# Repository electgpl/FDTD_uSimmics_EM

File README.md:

# qucs-em-viz

**EM simulation and visualization toolkit for RF structures on PCB: uSimmics / QucsStudio projects, KiCad boards and openEMS.**

Three independent scripts share one Python package (`qemviz/`). Each one solves a different problem in the design flow of an antenna or RF circuit on a PCB, from a 2D estimate in seconds to a full-wave 3D simulation of the board as manufactured.

*Left: 1×4 patch array of the HLK-LD2411 24 GHz radar (uSimmics flow). Right: 902–928 MHz directional coupler on FR4 (KiCad flow).*

---

## The three tools: which one do I use?

| Script | Input | Answers the question | Solver | Typical time |
|---|---|---|---|---|
| [`qucs_em_viz.py`](#1-qucs_em_vizpy--usimmics--qucsstudio-projects) | uSimmics `.pcb` + `.dat` | *How does the antenna I designed in uSimmics radiate, and what do its fields look like?* | uSimmics results; optional openEMS | seconds (minutes with openEMS) |
| [`kicad_em.py`](#2-kicad_empy--kicad-boards-n-port-full-wave) | KiCad `.kicad_pcb` + TOML sidecar | *How does the real board behave, with its connectors, pads, ground ring and vias?* | openEMS FDTD 3D | minutes |
| [`qs2d_mtl.py`](#3-qs2d_mtlpy--2d-quasi-static-solver--mtl) | Parameters in its CONFIG block | *What Z0, Z0e/Z0o, εeff and coupling do these line dimensions give?* | 2D Laplace + MTL | seconds |

**Suggested flow for an RF circuit (e.g. a directional coupler or a filter):**

```
 qs2d_mtl.py              uSimmics (+ qucs_em_viz.py)        KiCad layout              kicad_em.py            VNA
 size the lines      ->   design / iterate in the EM    ->   route the real    ->   verify the board   ->   measure and
 in seconds               solver, visualize results          board                  as manufactured         overlay .sNp
```

- **Antennas designed in uSimmics:** `qucs_em_viz.py`.
- **Couplers, filters, transitions or any N-port routed in KiCad:** `kicad_em.py`.
- **Quick dimensioning of single or coupled lines, or a reference curve for the 3D result:** `qs2d_mtl.py`.

All three scripts follow the same rules: parameters live in a `CONFIG` block at the top of the file, there are no command-line arguments (they run as-is from Thonny or any IDE), and relative paths are resolved from the script's own folder.

---

## Repository layout

```
qucs-em-viz/
├── qucs_em_viz.py          tool 1: uSimmics / QucsStudio projects
├── kicad_em.py             tool 2: KiCad boards -> openEMS N-port
├── qs2d_mtl.py             tool 3: 2D quasi-static + MTL
├── qemviz/                 shared package
│   ├── sexpr.py              S-expression reader (KiCad)
│   ├── model.py              neutral model: stackup, copper per layer, vias, ports, enclosure
│   ├── fe_kicad.py           KiCad front-end
│   ├── sidecar.py            TOML sidecar loader (stdlib tomllib) with defaults
│   ├── oe_backend.py         neutral model -> openEMS: mesh, boundaries, ports, N-port, cache
│   ├── fields.py             field dumps, |E| maps, phase animations (MP4/GIF)
│   ├── plots.py              layout, S-parameters, coupler metrics
│   ├── qs2d.py               2D quasi-static solver + MTL S-matrix
│   └── touchstone.py         .sNp writer / reader
├── examples/
│   ├── Radar24G_Array1x4_Layout.pcb / .dat     uSimmics example (24 GHz patch array)
│   └── coupler/
│       ├── DirectionalCoupler.kicad_pcb          KiCad example (4-port coupler)
│       └── DirectionalCoupler.toml               its sidecar
├── docs/img/               README figures
└── requirements.txt
```

`qucs_em_viz.py` is still a self-contained script. `kicad_em.py` and `qs2d_mtl.py` use the `qemviz/` package, so keep them next to that folder.

---

## Installation

```bash
pip install -r requirements.txt
```

| Package | Needed by |
|---|---|
| `numpy`, `matplotlib`, `pillow` | all |
| `h5py` | openEMS field dumps (tools 1 and 2) |
| `shapely` | `kicad_em.py` (polygon union, thermal-relief removal) |
| `scipy` | `qs2d_mtl.py` (sparse solver) |
| `imageio-ffmpeg` (optional) | MP4 animations in `kicad_em.py`, if `ffmpeg` is not in `PATH` |

### openEMS (tools 1 and 2)

The openEMS and CSXCAD Python bindings are not on PyPI. Install them from the [official openEMS releases](https://github.com/thliebig/openEMS-Project/releases) or build them following the [openEMS documentation](https://docs.openems.de/). The code was validated with openEMS v0.37.

**Windows:** since Python 3.8, DLLs are no longer searched in `PATH`. Both scripts register the openEMS folder automatically if they find `CSXCAD.dll` in `OE_DLL_DIR`, `%OPENEMS_INSTALL_PATH%`, `C:\openEMS` or `Program Files\openEMS`. If you get `DLL load failed while importing CSXCAD`, set in the CONFIG block:

```python
OE_DLL_DIR = r"C:\path\to\openEMS"   # folder containing openEMS.exe and CSXCAD.dll
```

---

## 1. `qucs_em_viz.py` — uSimmics / QucsStudio projects

Reads a uSimmics (formerly QucsStudio) **EM layout** project — the `.pcb` geometry and the binary `.dat` results — and produces layout, S11 and Smith chart, polar cuts and a 3D radiation pattern on top of the real copper. Through openEMS it also produces what uSimmics does not export: the **real near field** over the board, the surface current and the wave leaving the PCB. Ports, substrate and boundaries are taken from what you defined in uSimmics; nothing else has to be declared.

It is not tied to one antenna type: patch arrays, MIFA/IFA, printed dipoles, Yagis, filters and lines all work.

### Quick start

1. Simulate the layout in uSimmics (enable **Radiation** in the layout properties if you want the far-field from uSimmics).
2. In the CONFIG block:

```python
QUCS_DIR = r"C:\uSimmics\my_antenna"   # folder with the .pcb and .dat
PROJECT  = "my_antenna"                # base name of the files
```

3. Run it. Interactive windows open (the 3D pattern rotates with the mouse) and everything is saved to `<QUCS_DIR>/qucs_viz/`.

The repository is preconfigured to run `examples/Radar24G_Array1x4_Layout`.

### Outputs

| File | Content | Needs |
|---|---|---|
| `01_layout.png` | Copper from the `.pcb`, ports (with impedance), lumped shorts, size, substrate | `.pcb` |
| `02_s11.png` + `02_s11_<source>.csv` | \|S11\| in dB, ISM bands, −10 dB bandwidth; numeric export (f, S11, Zin) | `.dat` and/or openEMS |
| `03_smith.png` | S11 on a Smith chart | idem |
| `04_cuts_polar.png` | φ = 0° and φ = 90° cuts, HPBW, directivity | a pattern source |
| `05_pattern_3d.png` | 3D pattern (dB colormap) on the real copper | a pattern source |
| `06_field_map_db.png`, `wave.gif` | \|E\|·r and Re{E·e^jωt} on a vertical plane | a pattern source |
| `07_nearfield_E_top.png`, `nearfield.gif` | Real \|E\| just above the copper, static and animated | openEMS |
| `08_surface_current_J.png` | Current density \|J\| on the copper | openEMS |
| `09_nearfield_E_side.png`, `nearfield_side.gif` | \|E\|·r and the real wave on a vertical plane | openEMS |
| `pattern_3d_rot.gif` | Rotating 3D pattern (off by default) | `MAKE_ROT_GIF = True` |

### Pattern sources

`PATTERN_SOURCE = "auto"` tries, in order:

| Source | What it is | When |
|---|---|---|
| `dat` | Far-field computed by uSimmics (Radiation enabled) | Preferred whenever available; valid for any antenna |
| `openems` | Own openEMS run built from the `.pcb` primitives, with NF2FF and field dumps | Near fields and currents, or no far-field in the `.dat` |
| `patch` | Analytical patch (cavity model) × array factor | Quick look at patch arrays only |
| `none` | Layout and S-parameters only | — |

With a far-field in the `.dat`, openEMS is skipped unless `OE_NEARFIELD_ALWAYS = True` (then the pattern still comes from uSimmics and openEMS adds figures 07–09). The field map synthesized from a far-field is masked for `r < max(λ/2π, antenna size)`; between that radius and 2D²/λ it is an approximation (Fresnel region).

### Configuration

| Parameter | Default | Meaning |
|---|---|---|
| `PATTERN_SOURCE` | `"auto"` | `auto`, `dat`, `openems`, `patch`, `none` |
| `F_PATTERN_HZ` | `None` | Pattern frequency; `None` = Radiation frequency of the `.pcb` if inside the sweep, otherwise the S11 minimum |
| `CUT_PHI_DEG` | `None` | Plane for the field maps; `None` = plane of the narrowest beam |
| `DB_RANGE` | `30` | Dynamic range of the dB plots |
| `FIELD_HALF_LAM`, `FIELD_RES_LAM` | `5`, `1/30` | Size and resolution of the far-field-based map, in λ₀ |
| `MAKE_GIFS`, `MAKE_ROT_GIF`, `N_FRAMES` | `True`, `False`, `24` | Animations |
| `SHOW`, `SHOW_WAVE_LIVE` | `True`, `True` | Interactive windows |
| `PATCH_REGEX`, `POL_AXIS`, `ELEM_PHASE_DEG`, `ELEM_AMPL` | | Analytical patch model |
| `OE_ENABLE` | `True` | Allow openEMS in `auto` mode |
| `OE_NEARFIELD_ALWAYS` | `False` | Run openEMS for figures 07–09 even if the `.dat` has a far-field |
| `OE_GROUND` | `"auto"` | Bottom ground: follows the substrate backside flag of the `.pcb`; or `"full"`, `"none"`, `"largest"`, list of rectangles (m) |
| `OE_EXTRA_TOP` | `[]` | Extra top copper (m), e.g. the rest of the board ground |
| `OE_RES_MM` | `None` | Fine cell; `None` = half of the narrow traces, ≥ 2 cells per port |
| `OE_END_DB`, `OE_MAX_TS` | `-30`, `400000` | End criterion and timestep limit |
| `OE_AIR_LAM`, `OE_AIR_UP_LAM` | `0.25`, `1.0` | Air around / above the board, in λ at the lowest frequency |
| `OE_NEAR_DZ_MM`, `OE_N_FDUMP` | `0.5`, `21` | Height of the \|E\| plane, number of dump frequencies |
| `OE_WRITE_XML`, `OE_OPEN_APPCSXCAD`, `OE_VTK_DUMPS` | `True`, `False`, `False` | Model XML for AppCSXCAD; open it; time-domain VTK for ParaView |
| `OE_FORCE_RERUN` | `False` | Ignore the cache |

openEMS results are cached in `qucs_viz/openems_<hash>/`; the hash covers the `.pcb`, the openEMS settings and the backend version.

### How the uSimmics files are read

**`.pcb` (text):** `Rectangle NAME x y dx|dy|w|h` → copper in `[x+dx, x+dx+w] × [y+dy, y+dy+h]` (m). `Lumped NAME x y num dir Z … wx wy` → `num > 0` is a port, `num = 0` a lumped element (0 Ω = via to ground); `wx`, `wy` are the element widths. `Substrate` (εr, h, tan δ, copper thickness, backside metal flag), `Frequency` and `Radiation` complete the setup. Only `Rectangle` and `Lumped` primitives are supported for now.

**`.dat` (binary QucsData):** `"QucsData"` + 4 bytes + `int32` header length, header entries `[int32 type][int32 N][name\0][dependencies\0]`, then the data blocks in the same order. Block sizes come from the type code (3 = complex dependent, 7 = real dependent, 5 = real independent); for unknown codes the parser tries the combinations that match the file size exactly. Far-field axes `theta/phi` or `azimuth/elevation` are both recognized.

### Validation: 24 GHz patch array (`examples/`)

uSimmics FDTD vs. this openEMS backend (0.085 mm fine cell, 2.0 Mcells, −30 dB end criterion):

| | uSimmics | openEMS backend |
|---|---|---|
| S11 minimum | −15.53 dB @ 24.714 GHz | −16.71 dB @ 24.425 GHz |
| Zin at minimum | 41.6 − j13.0 Ω | 42.5 − j11.3 Ω |
| −10 dB bandwidth | 367 MHz | 443 MHz |

The ≈1.2 % resonance shift is consistent with two FDTD runs on different meshes over 0.17 mm traces. NF2FF at 24.125 GHz: D = 10.4 dBi, HPBW 37.6° (array plane) and 78.0° (orthogonal plane). The far-field parser was also checked with a synthetic `.dat` of an ideal short dipole: D = 1.76 dBi, HPBW = 90°.

---

## 2. `kicad_em.py` — KiCad boards, N-port full-wave

Reads a **KiCad 9 `.kicad_pcb`** directly (no KiCad installation or CLI needed) and simulates the board as manufactured in openEMS: SMA pads, tapers, ground rings and stitching vias included. It produces the full S-matrix, a Touchstone file to overlay with a VNA, coupler metrics, \|E\| maps and phase animations.

### What is defined where

KiCad only provides the **geometry**. Everything KiCad does not store goes in a **TOML sidecar** next to the board. There is nothing special to draw in KiCad.

| What | Where |
|---|---|
| Copper, vias, pads, board outline | `.kicad_pcb` |
| Material (εr, tan δ, thickness) | KiCad *Board Setup → Physical Stackup* if filled in; otherwise `[stackup]` in the sidecar |
| Ports | Automatic from coaxial-connector footprints; manual in `[ports]` |
| Excitation | Automatic: each port is excited in turn |
| Test environment (box, air, lid) | `[enclosure]` |
| Frequency sweep and band of interest | `[sweep]` |
| Mesh, field maps, animations | CONFIG block of `kicad_em.py` |

### Quick start

The repository is preconfigured with the coupler example. Open `kicad_em.py` and run it:

```python
KICAD_PCB = "examples/coupler/DirectionalCoupler.kicad_pcb"
SIDECAR   = "examples/coupler/DirectionalCoupler.toml"
OUT_DIR   = "examples/coupler/em_out"
```

For a new board:

1. Create a folder, e.g. `examples/filter_915/`, and put your `.kicad_pcb` in it.
2. Copy `DirectionalCoupler.toml` there with a new name and adapt `[stackup]`, `[sweep]`, `[enclosure]` and the port `order` (remove `[roles]` if it is not a coupler).
3. Point `KICAD_PCB`, `SIDECAR` and `OUT_DIR` to the new files and run.
4. **Check `01_layout.png` first**: every port (numbered red dot) must sit at the end of its connector pad, on the board edge. Fix any port with `[[ports.override]]` before trusting the results.

The first run simulates (a few minutes per excitation for the coupler); later runs use the cache and finish in seconds.

### Sidecar reference

```toml
name = "DirectionalCoupler"

[stackup]                 # used when the .kicad_pcb has no Physical Stackup
er = 4.4
tand = 0.02
h = 1.6                   # mm

[sweep]
f_start = 0.3e9
f_stop = 3.0e9
n_points = 541
band = [902e6, 928e6]     # shaded in the plots; also where tan(delta) is exact (see notes)

[geometry]
# roi = [110, 95, 170, 122]   # clip box in KiCad mm (optional)
thermal_close_mm = 0.3        # removes thermal reliefs (per-net morphological closing)
simplify_mm = 0.02

[ports]
auto = true               # from SMA / U.FL / MMCX / SMB / ... footprints, pad "1"
kind = "lumped"           # "lumped" (validated) | "msl" (experimental, not validated yet)
z0 = 50.0
order = ["J1", "J2", "J3", "J4"]   # port numbering: Port 1 = J1, ...

# Manual port (or override of an auto-detected one: same name = only the given fields change)
# [[ports.override]]
# name  = "IN"
# x     = 102.0          # KiCad mm
# y     = 102.0
# prop  = "+x"           # direction INTO the structure: "+x" "-x" "+y" "-y" (KiCad: +y = down)
# width = 3.0            # conductor width at the port
# z0    = 50.0

[roles]                   # only for couplers: enables coupling / isolation / directivity plots
input = "J1"
through = "J2"
coupled = "J3"
isolated = "J4"

[enclosure]
kind = "pec_box"          # closed metal box | "open" = free space with PML_8
air = 4.8                 # mm of air above the top copper
lid_h = 1.6               # lid dielectric thickness (0 = no lid)
lid_er = 4.4
lid_tand = 0.02
lid_metal = true          # copper on the outer face of the lid
# box = [100, 82, 180, 122]       # PEC side walls (KiCad mm); default = board outline
# frame_er = 4.4                  # dielectric frames between walls and an inner window
# frame_window = [103, 85, 177, 119]
```

**Ports.** Auto-detection takes pad "1" of every footprint whose library name matches SMA, U.FL, MMCX, SMB, SMP, IPEX or Coaxial. The reference plane is the end of the pad closest to the board edge, and the port is a vertical lumped port from the trace to the copper layer below. For boards without connectors (a filter between two traces, a section of a larger board), declare the ports manually.

**Excitation.** Nothing to declare. For the full S-matrix every port is excited in turn with a Gaussian pulse covering `[sweep]`, while the other ports are terminated in their Z0. With `SYMMETRY = "mirror_x"` (or `"mirror_y"`) in the CONFIG block the script pairs the ports by position and only excites one port per pair. `DUMP_PORT` selects which excitation is used for the field maps.

### Outputs (in `OUT_DIR`)

| File | Content |
|---|---|
| `01_layout.png` | Copper (top and bottom), vias, ports with their numbers, in KiCad coordinates |
| `02_sparams.png` | All \|Sij\| vs. frequency |
| `03_coupler_metrics.png` | Coupling, isolation, directivity, return loss, insertion loss, band shaded, overlays (MTL, VNA) — if `[roles]` is defined |
| `<name>.sNp` | Touchstone (RI, Hz, 50 Ω) |
| `04_E_top_<f>.png` | \|E\| top view in dB, turbo colormap, copper contours |
| `05_E_phase_<f>.mp4` / `.gif` | \|E(t)\| = \|Re{E·e^jφ}\| over one RF period: MP4 1920×1080, 24 fps, H.264 crf 16, 72 frames, plus GIF preview |
| `06_E_profile_<f>.png` | \|E\| along the lines listed in `PROFILES` |
| `oe_<hash>_exc<n>_model.xml` | openEMS model of each run (open it in AppCSXCAD to inspect geometry, mesh and ports) |

The console prints the in-band reciprocity error and a table of C / I / D / RL / IL at the band edges, band centre, 915 MHz and 1830 MHz for every overlaid source.

### Configuration

| Parameter | Default | Meaning |
|---|---|---|
| `KICAD_PCB`, `SIDECAR`, `OUT_DIR` | example | Input board, sidecar, output folder |
| `OE_DLL_DIR` | `None` | openEMS folder on Windows, if not found automatically |
| `SYMMETRY` | `"mirror_x"` | `None`, `"mirror_x"`, `"mirror_y"` |
| `FORCE_RERUN` | `False` | Ignore the cache |
| `MESH["res_mm"]` | `0.5` | Fine cell at copper edges (thirds rule) |
| `MESH["lambda_div"]` | `20` | Max cell = λ/20 at `f_stop` in the densest dielectric |
| `MESH["max_board_mm"]` | `1.0` | Max x/y cell (≥ 3 cells across gaps of coupled lines) |
| `MESH["n_sub"]`, `MESH["n_lid"]` | `4`, `2` | Cells across substrate and lid |
| `MESH["end_db"]`, `MESH["max_ts"]` | `-40`, `1e6` | End criterion and timestep limit |
| `DUMP_Z_FRAC` | `0.25` | Dump plane depth below the top copper, as a fraction of h |
| `DUMP_FREQS`, `DUMP_PORT` | `[915e6, 1830e6]`, `1` | Frequencies and excitation of the field maps |
| `VTK_TIME_DUMP` | `False` | Time-domain VTK of the same plane (ParaView animation of the pulse) |
| `MAKE_MP4`, `MAKE_GIF`, `ANIM_FRAMES` | `True`, `True`, `72` | Animations |
| `DB_RANGE` | `50` | Dynamic range of the \|E\| maps |
| `PROFILES` | coupled line | \|E\| cuts: `(label, (x0, y0), (x1, y1))` in KiCad mm |
| `OVERLAY_S4P` | MTL result | Extra Touchstone files plotted with the openEMS result (MTL, VNA) |

### Modelling notes

- **Coordinates:** KiCad's y points down; the model flips it internally and all plots and sidecar coordinates use KiCad coordinates.
- **Copper:** zero-thickness PEC sheets; segments with round caps; arcs every 10°; per-net union with morphological closing (removes thermal reliefs); polygons with holes are split for CSXCAD. Silkscreen, fab, courtyard, mask and text are ignored.
- **Vias:** z-directed PEC wires snapped to the nearest mesh line (no extra mesh lines, never silently dropped).
- **Mesh:** thirds rule (1/3 inside, 2/3 outside) on axis-aligned copper edges, `n_sub` cells per substrate, λ/20 limit, smoothing ratio 1.4, merging of near-coincident lines while keeping copper and port edges.
- **Boundaries:** `pec_box` = PEC on all six faces (the lid's outer copper is the top wall); `open` = PML_8 with λ/4 of air at the lowest frequency.
- **Dielectric loss:** openEMS models tan δ as a constant conductivity κ = 2πf·ε0·εr·tan δ, exact at one frequency only (tan δ_eff = tan δ·f_loss/f). The script sets f_loss at the centre of `band`; without it, the loss at the band would be wrong by the ratio of frequencies.

### Validation: directional coupler (`examples/coupler/`)

80 × 40 mm FR4 (εr 4.4, tan δ 0.02, 1.6 mm), 3 mm lines with a 3 mm gap, 38 mm coupled section, PEC box on the board outline, 4.8 mm of air, FR4 lid with outer copper, lumped 50 Ω ports at the SMA pad ends. Values at 915 MHz.

| Quantity | 2D/MTL (`qs2d_mtl.py`) | openEMS (`kicad_em.py`) |
|---|---|---|
| Z0 / Z0e / Z0o [Ω] | 48.9 / 51.1 / 46.8 | — |
| εeff,e / εeff,o | 3.354 / 3.097 | — |
| Coupling [dB] | 27.43 | 27.86 |
| Isolation [dB] | 31.74 | 31.29 |
| Directivity [dB] | 4.31 | 3.43 |
| Return loss [dB] | 32.9 | 20.5 |
| Insertion loss [dB] | 0.11 | 0.28 |
| Coupling peak | 27.10 dB @ 1.105 GHz | 27.55 dB @ 1.140 GHz |
| Directivity @ 1830 MHz [dB] | −7.0 | −8.9 |

Coupling and isolation agree within 0.5 dB. Return loss and insertion loss differ by construction: the MTL models only the straight coupled section, while openEMS includes the SMA pad launches (1.27 mm pad, taper and coplanar ground pads), the lumped-port inductance and the feed lines. In-band reciprocity error of the openEMS S-matrix: 1.2·10⁻³.

---

## 3. `qs2d_mtl.py` — 2D quasi-static solver + MTL

Two steps, no 3D simulation:

1. **2D quasi-static solver:** finite differences of ∇·(ε∇φ) = 0 on the cross-section of the lines, with layered dielectrics, an optional metal cover and side walls. Outputs per-unit-length C, L, G matrices and **Z0, Z0e/Z0o, εeff,e/εeff,o**: what a line calculator gives, but with enclosure, lid and multiple dielectrics.
2. **MTL model:** exact chain matrix of the coupled section (inhomogeneous lines, so different even and odd phase velocities) → 4-port S-matrix, exported as `.s4p`.

Use it to dimension lines in seconds (change width, gap, length or lid height and see coupling, directivity and the λ/4 frequency move), and as a reference curve for `kicad_em.py`, which overlays the `.s4p` automatically. Its geometry does not come from a PCB file: the cross-section is defined in the CONFIG block.

### Configuration

| Parameter | Example (coupler) | Meaning |
|---|---|---|
| `WIDTH_MM`, `SIDE_WALLS` | `40.0`, `True` | Cross-section width and PEC side walls |
| `H_MM`, `ER`, `TAND` | `1.6`, `4.4`, `0.02` | Substrate |
| `AIR_MM` | `4.8` | Air between top copper and lid |
| `LID_MM`, `LID_ER`, `LID_TAND`, `LID_METAL` | `1.6`, `4.4`, `0.02`, `True` | Lid (0 = none) and its outer copper (False = open top) |
| `STRIPS_MM` | `[(18.5, 21.5), (24.5, 27.5)]` | (y0, y1) of line 1 (main) and line 2 (coupled), from the left wall |
| `COUPLED_LEN_MM` | `38.0` | Length of the coupled section |
| `GRID_MM` | `0.05` | FD cell (≈1 % on Z0, a few seconds) |
| `F_START`, `F_STOP`, `N_POINTS`, `BAND` | | Sweep of the MTL S-matrix |
| `VARIANTS` | `True` | Also print lid → air and no-lid variants |
| `OUT_S4P` | `examples/coupler/em_out/mtl_qs2d.s4p` | Output Touchstone (ports: input, through, coupled, isolated) |

### Validation

Isolated 3 mm microstrip on 1.6 mm FR4 (εr 4.4): 50.5 Ω vs. 50.65 Ω from Hammerstad–Jensen (0.2 %), converging with the grid (48.71 → 48.88 → 48.97 Ω for 0.1 / 0.05 / 0.025 mm on the shielded coupler). For the coupler: removing the lid gives 24.4 dB of coupling instead of 27.4 dB, and replacing the FR4 lid by air changes it by 0.2 dB.

---

## Overlaying VNA measurements

`qemviz/touchstone.py` reads `.sNp` files in RI, MA or DB format (Hz to GHz). Add the measured file to `OVERLAY_S4P` in `kicad_em.py` and it is plotted next to the openEMS and MTL curves, and included in the console table. Keep the port order of the measurement consistent with `[ports] order` in the sidecar.

---

## Limitations and pitfalls

**uSimmics flow (`qucs_em_viz.py`)**

- **Substrate backside metal (the most common mistake with printed antennas).** A metal backside places a ground plane under the *entire* layout. That is correct for microstrip patches, but an IFA/MIFA/printed dipole over a full ground does not radiate (Re(Zin) of a few ohms or less, inductive Zin). The script reads the flag and warns. For printed antennas, remove the backside metal and draw the real board ground as copper.
- **Schematic and layout sharing the same dataset.** With `DataSet=*.dat`, `name.sch` and `name.pcb` both write `name.dat` and overwrite each other. Give the EM layout its own name; the script warns when it finds a `.sch` with the same base name.
- **Schematic-generated layouts.** Circuit models (MLIN, MTEE…) assume an infinite ground under every line and do not radiate. A printed antenna designed in the schematic is, for the circuit simulator, a resonator over ground. Size printed antennas in the EM layout, with the real board ground. Lumped matching networks drawn in the schematic are not part of the generated layout.
- **Ground definition for openEMS.** The `.pcb` does not fully describe the ground assumed by uSimmics; `OE_GROUND` / `OE_EXTRA_TOP` set it. Compare the two S11 curves before trusting the openEMS near-field figures.
- **Mismatched antennas.** NF2FF patterns are normalized and keep a shape even when almost no power enters. The script warns when S11 > −3 dB and when \|S11\| = 1 everywhere.
- Only `Rectangle` and `Lumped` primitives; multi-port S-matrix ordering in the `.dat` not yet verified with a real file.

**KiCad flow (`kicad_em.py`)**

- **MSL ports are experimental:** implemented but not validated (on the coupler they gave \|Sii\| = 1). Use `kind = "lumped"`.
- Two copper layers validated (top signal, bottom ground). Multilayer stack-ups are read from the Physical Stackup but not validated yet.
- Mesh lines follow axis-aligned copper edges; 45° and curved edges are staircased at the mesh resolution.
- The SMA connector body is not modelled: the reference plane is the pad end. Compare with a VNA after de-embedding the connector, or at least with port extension.
- Enclosure frames whose vias are not bonded by copper are not a true PEC wall; `pec_box` is an idealization. The `frame_er` / `frame_window` option exists but has not been validated.

**2D/MTL (`qs2d_mtl.py`)**

- Only the uniform coupled section: bends, chamfers, launches and feed lines are not modelled. Zero-thickness strips; R = 0 (no conductor loss).

---

## Troubleshooting

| Symptom | Tool | Cause / fix |
|---|---|---|
| `DLL load failed while importing CSXCAD` | 1, 2 | Set `OE_DLL_DIR` (see Installation) |
| `No module named 'qemviz'` | 2, 3 | Keep the script next to the `qemviz/` folder |
| `No module named 'shapely'` / `'scipy'` | 2 / 3 | `pip install shapely` / `pip install scipy` |
| `WARNING: port … is not connected` / S11 flat at 0 dB | 1, 2 | Port not touching the copper in the mesh: check `01_layout.png`, reduce the fine cell |
| Port in the wrong place or wrong direction | 2 | Fix it with `[[ports.override]]` (KiCad coordinates, `prop` into the structure) |
| `ffmpeg not found … MP4 skipped` | 2 | `pip install imageio-ffmpeg` or put ffmpeg in `PATH`; the GIF is still written |
| `ERROR generating … (Pillow installed?)` | 1 | `pip install pillow` |
| No 3D / pattern figures | 1 | No pattern source: enable Radiation in uSimmics, or allow openEMS |
| Finishes in seconds without near-field figures | 1 | The `.dat` already has a far-field: set `OE_NEARFIELD_ALWAYS = True` |
| Very long openEMS run | 1, 2 | Relax the end criterion to −30 dB, coarsen the mesh, reduce the air; results are cached after the first run |

---

## Credits

- [openEMS](https://openems.de/) / CSXCAD — Thorsten Liebig and contributors (FDTD engine, NF2FF).
- uSimmics / QucsStudio — Michael Margraf.
- Patch cavity model after C. A. Balanis, *Antenna Theory: Analysis and Design*, 4th ed., ch. 14.
- Microstrip reference formulas: E. Hammerstad and Ø. Jensen, "Accurate models for microstrip computer-aided design", IEEE MTT-S, 1980.

Developed by **ELECTGPL** (electronics, RF and embedded systems channel on YouTube).

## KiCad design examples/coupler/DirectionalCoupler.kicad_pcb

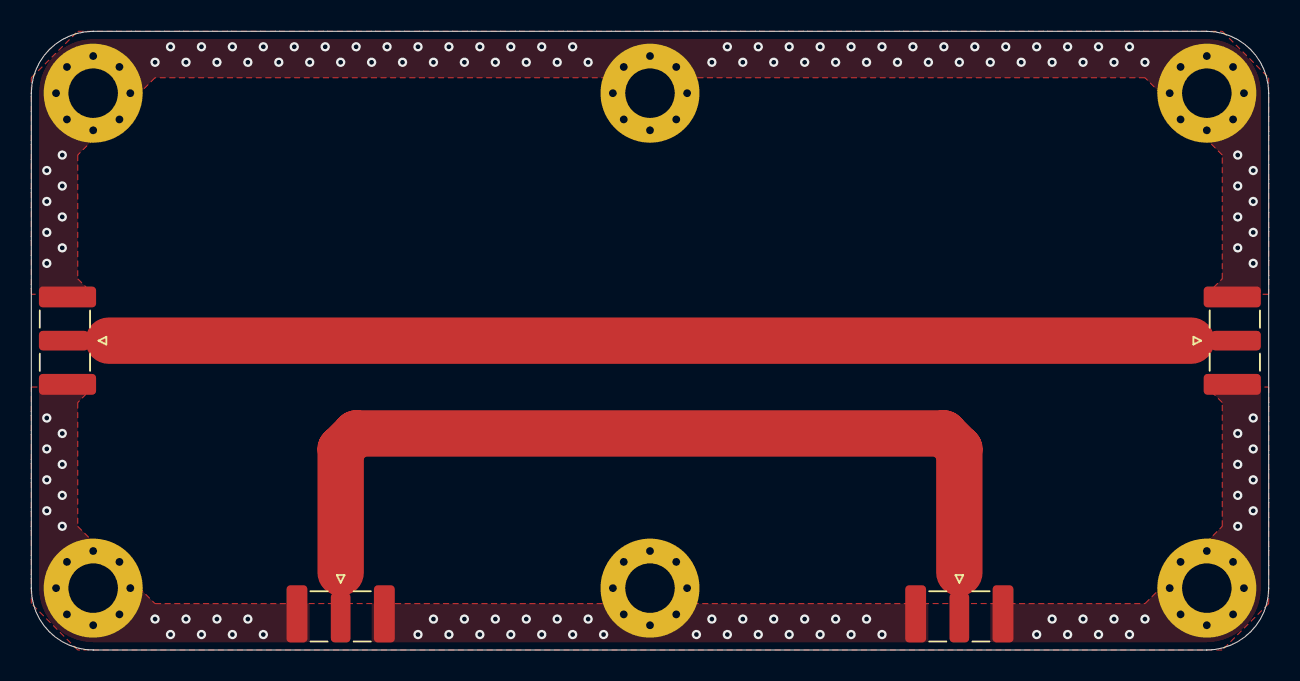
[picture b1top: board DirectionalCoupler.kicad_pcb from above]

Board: 2 copper layers, 80.0 x 40.0 mm, 10 parts (0 on the bottom side), 3 nets.

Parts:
H1, H2, H3, H4, H5, H6: MountingHole_Pad; MountingHole_3.2mm_M3_Pad_Via
J1, J2, J3, J4: Conn_Coaxial; SMA_Samtec_SMA-J-P-H-ST-EM1_EdgeMount

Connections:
GND: H1.1, H2.1, H3.1, H4.1, H5.1, H6.1, J1.2 (Ext), J2.2 (Ext), J3.2 (Ext), J4.2 (Ext)
unnamed: J1.1 (In), J2.1 (In)
unnamed: J3.1 (In), J4.1 (In)
